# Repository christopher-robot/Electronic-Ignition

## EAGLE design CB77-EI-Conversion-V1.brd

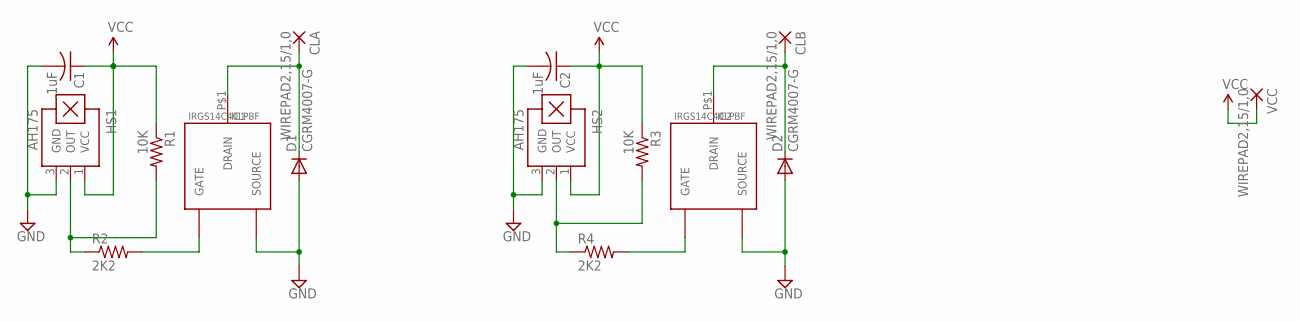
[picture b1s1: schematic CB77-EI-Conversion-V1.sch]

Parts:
C1, C2: .1uF; C0603K
CLA: WIREPAD2,15/1,0; 2,15/1,0
CLB: WIREPAD2,15/1,0; 2,15/1,0
D1, D2: CGRM4007-G; SOD-123_MINI-SMA
HS1, HS2: AH175; SOT23-W
IC1, IC2: IRGS14C40LPBF; TO-263AB
R1, R3: 10K; R0603
R2, R4: 2K2; R0603
VCC: WIREPAD2,15/1,0; 2,15/1,0

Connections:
G1: IC1.P$2 (GATE), R2.2
G2: IC2.P$2 (GATE), R4.2
GND: C1.2, C2.2, D1.A, D2.A, HS1.3 (GND), HS2.3 (GND), IC1.P$3 (SOURCE), IC2.P$3 (SOURCE)
LHS: CLB.1, D2.C, IC2.P$1 (DRAIN)
unnamed: HS1.2 (OUT), R1.2, R2.1
unnamed: HS2.2 (OUT), R3.2, R4.1
RHS: CLA.1, D1.C, IC1.P$1 (DRAIN)
VCC: C1.1, C2.1, HS1.1 (VCC), HS2.1 (VCC), R1.1, R3.1, VCC.1

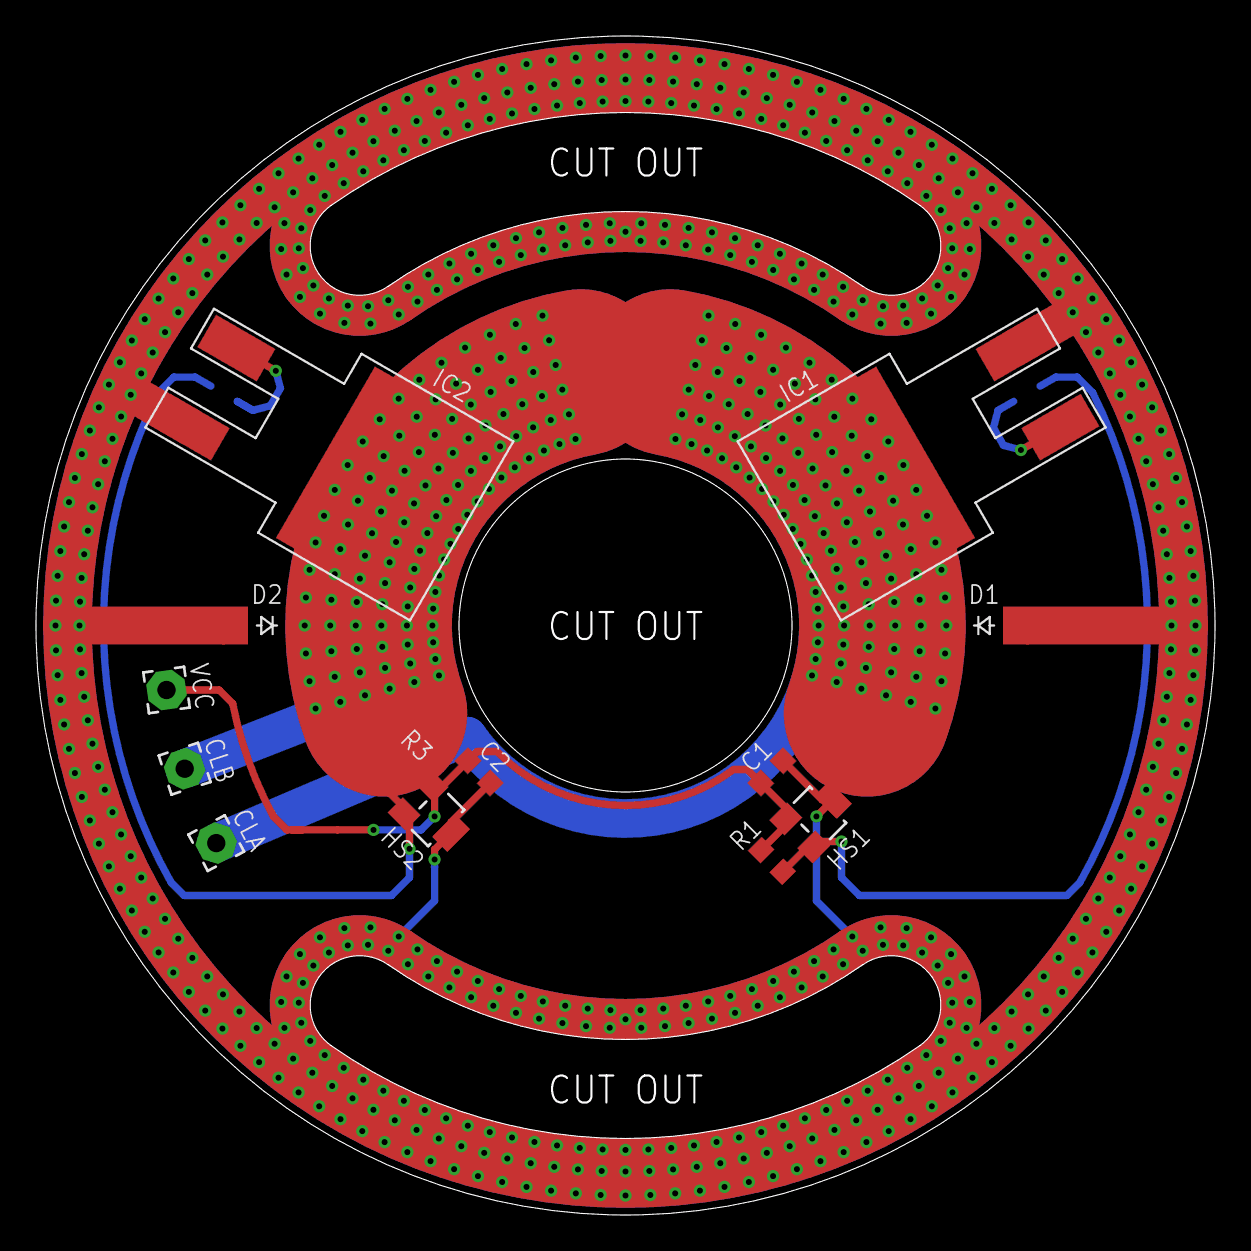
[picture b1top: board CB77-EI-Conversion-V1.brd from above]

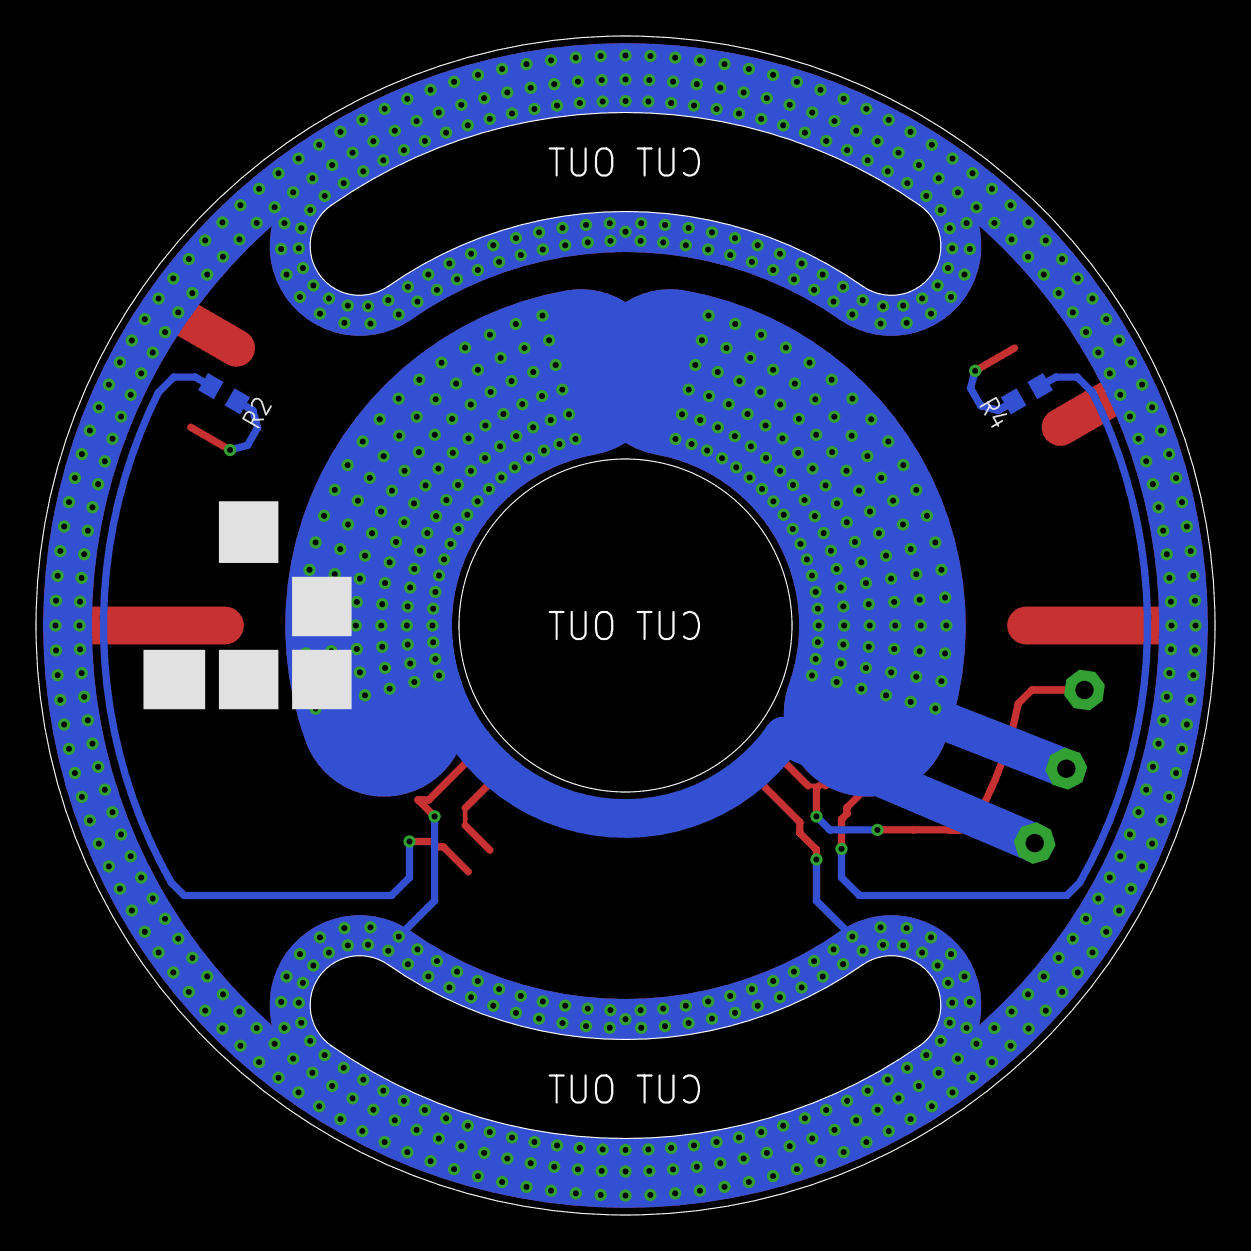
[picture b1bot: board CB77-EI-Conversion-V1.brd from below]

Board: 2 copper layers, 65.5 x 65.5 mm, 16 parts (3 on the bottom side), 8 nets.

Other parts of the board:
U$1: GLIDER3

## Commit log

2015-08-15 V1 initial release

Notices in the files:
parts and their libraries:
SparkFun-Aesthetics: Licensing: CC v3.0 Share-Alike You are welcome to use this library for commercial purposes.
